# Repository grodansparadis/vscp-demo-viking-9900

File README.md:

# vscp-demo-viking-9900
PLC interface for Viking 9900 pellets burner to CAN4VSCP Beijing and Accra modules

**Note!** This is still a prototype.

## PCB's

---

Part of the [VSCP Project](https://www.vscp.org).

Copyright 2021-2022 © Åke Hedman, (Grodans Paradis AB)[https://www.grodansparadis.com]

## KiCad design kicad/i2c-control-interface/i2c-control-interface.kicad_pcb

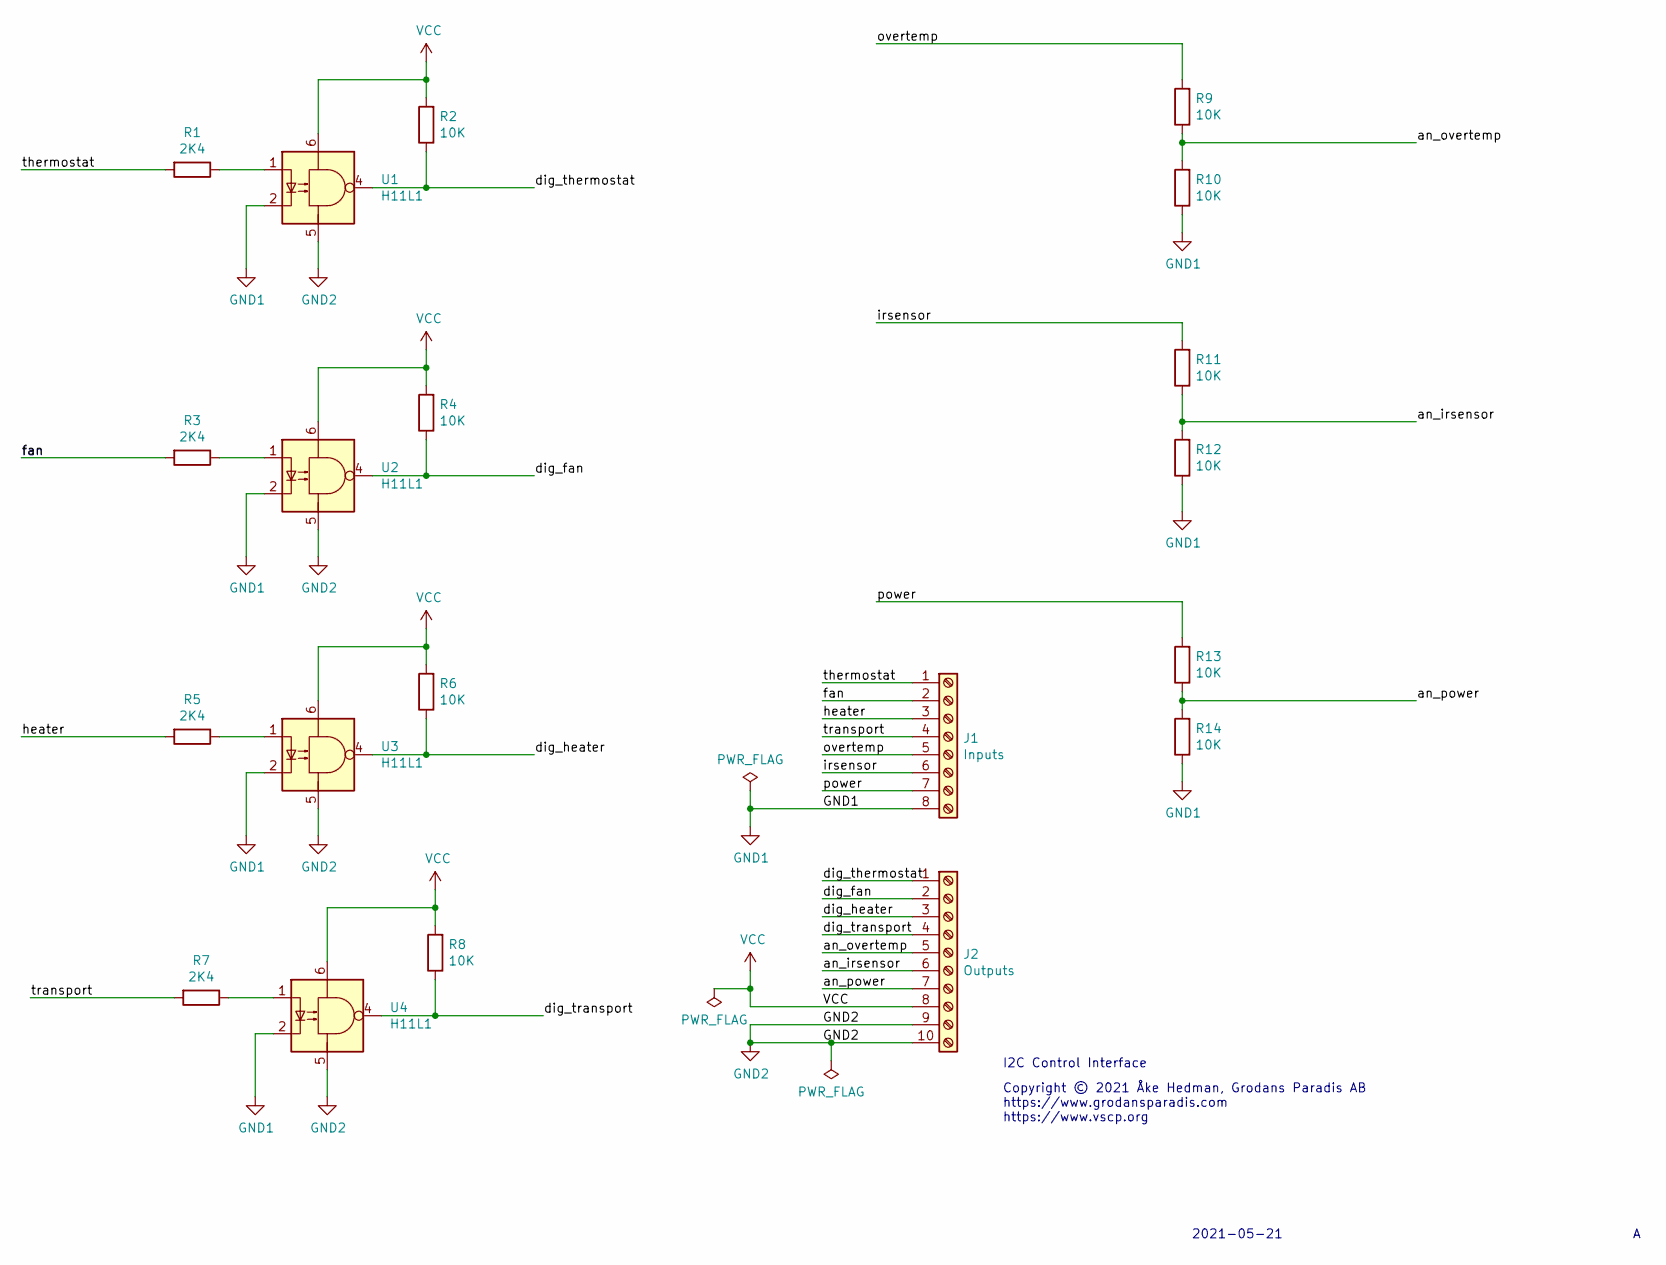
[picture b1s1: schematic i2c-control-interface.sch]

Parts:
J1: Inputs; PinHeader_1x08_P2.54mm_Vertical
J2: Outputs; PinHeader_1x10_P2.54mm_Vertical
R1, R3, R5, R7: 2K4; R_0805_2012Metric
R2, R4, R6, R8, R9, R10, R11, R12, R13, R14: 10K; R_0805_2012Metric
U1, U2, U3, U4: H11L1; DIP-6_W7.62mm_SMDSocket_SmallPads

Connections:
/an_irsensor: J2.6, R11.1, R12.2
/an_overtemp: J2.5, R9.1, R10.2
/an_power: J2.7, R13.1, R14.2
/dig_fan: J2.2, R4.1, U2.4
/dig_heater: J2.3, R6.1, U3.4
/dig_thermostat: J2.1, R2.1, U1.4
/dig_transport: J2.4, R8.1, U4.4
/fan: J1.2, R3.2
/heater: J1.3, R5.2
/irsensor: J1.6, R11.2
/overtemp: J1.5, R9.2
/power: J1.7, R13.2
/thermostat: J1.1, R1.2
/transport: J1.4, R7.2
GND1: J1.8, R10.1, R12.1, R14.1, U1.2, U2.2, U3.2, U4.2
GND2: J2.9, J2.10, U1.5, U2.5, U3.5, U4.5
unnamed: R1.1, U1.1
unnamed: R3.1, U2.1
unnamed: R5.1, U3.1
unnamed: R7.1, U4.1
VCC: J2.8, R2.2, R4.2, R6.2, R8.2, U1.6, U2.6, U3.6, U4.6

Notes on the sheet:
I2C Control Interface
2021-05-21
Copyright © 2021 Åke Hedman, Grodans Paradis AB https://www.grodansparadis.com https://www.vscp.org
fan

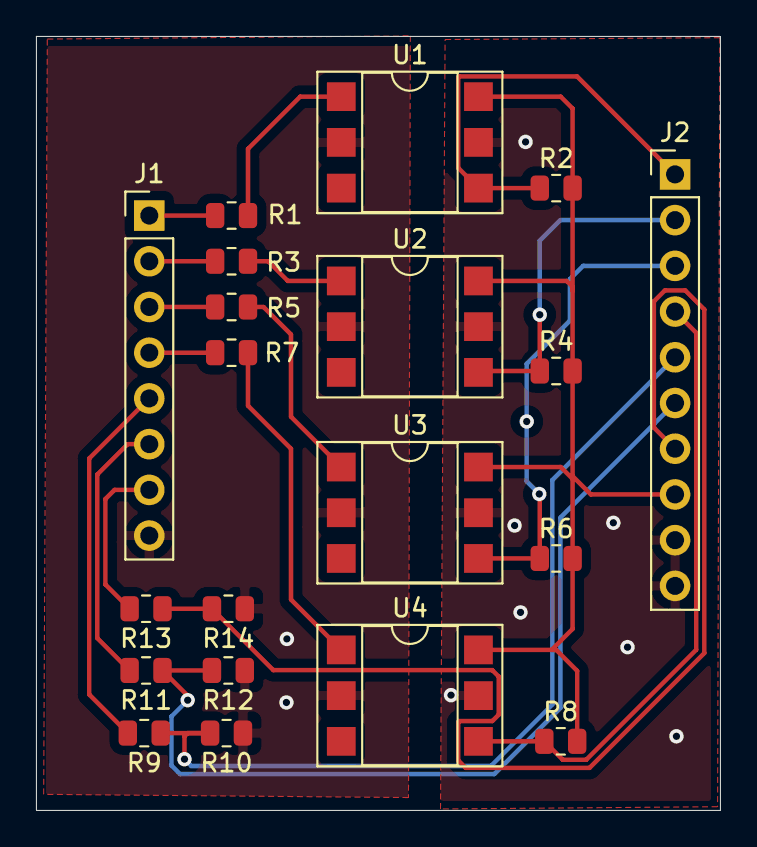
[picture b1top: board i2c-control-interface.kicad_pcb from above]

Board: 2 copper layers, 38.0 x 43.0 mm, 20 parts (0 on the bottom side), 21 nets.

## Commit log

2021-05-21 Added eagle folder
2021-05-21 Rev A
2021-05-25 Added gerbers
2021-05-25 Added info
2021-05-25 Added copyright info
2022-02-03 Updated copyright

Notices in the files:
kicad/i2c-control-interface/i2c-control-interface.kicad_pcb:
Copyright © Åke Hedman, Grodans Paradis AB
